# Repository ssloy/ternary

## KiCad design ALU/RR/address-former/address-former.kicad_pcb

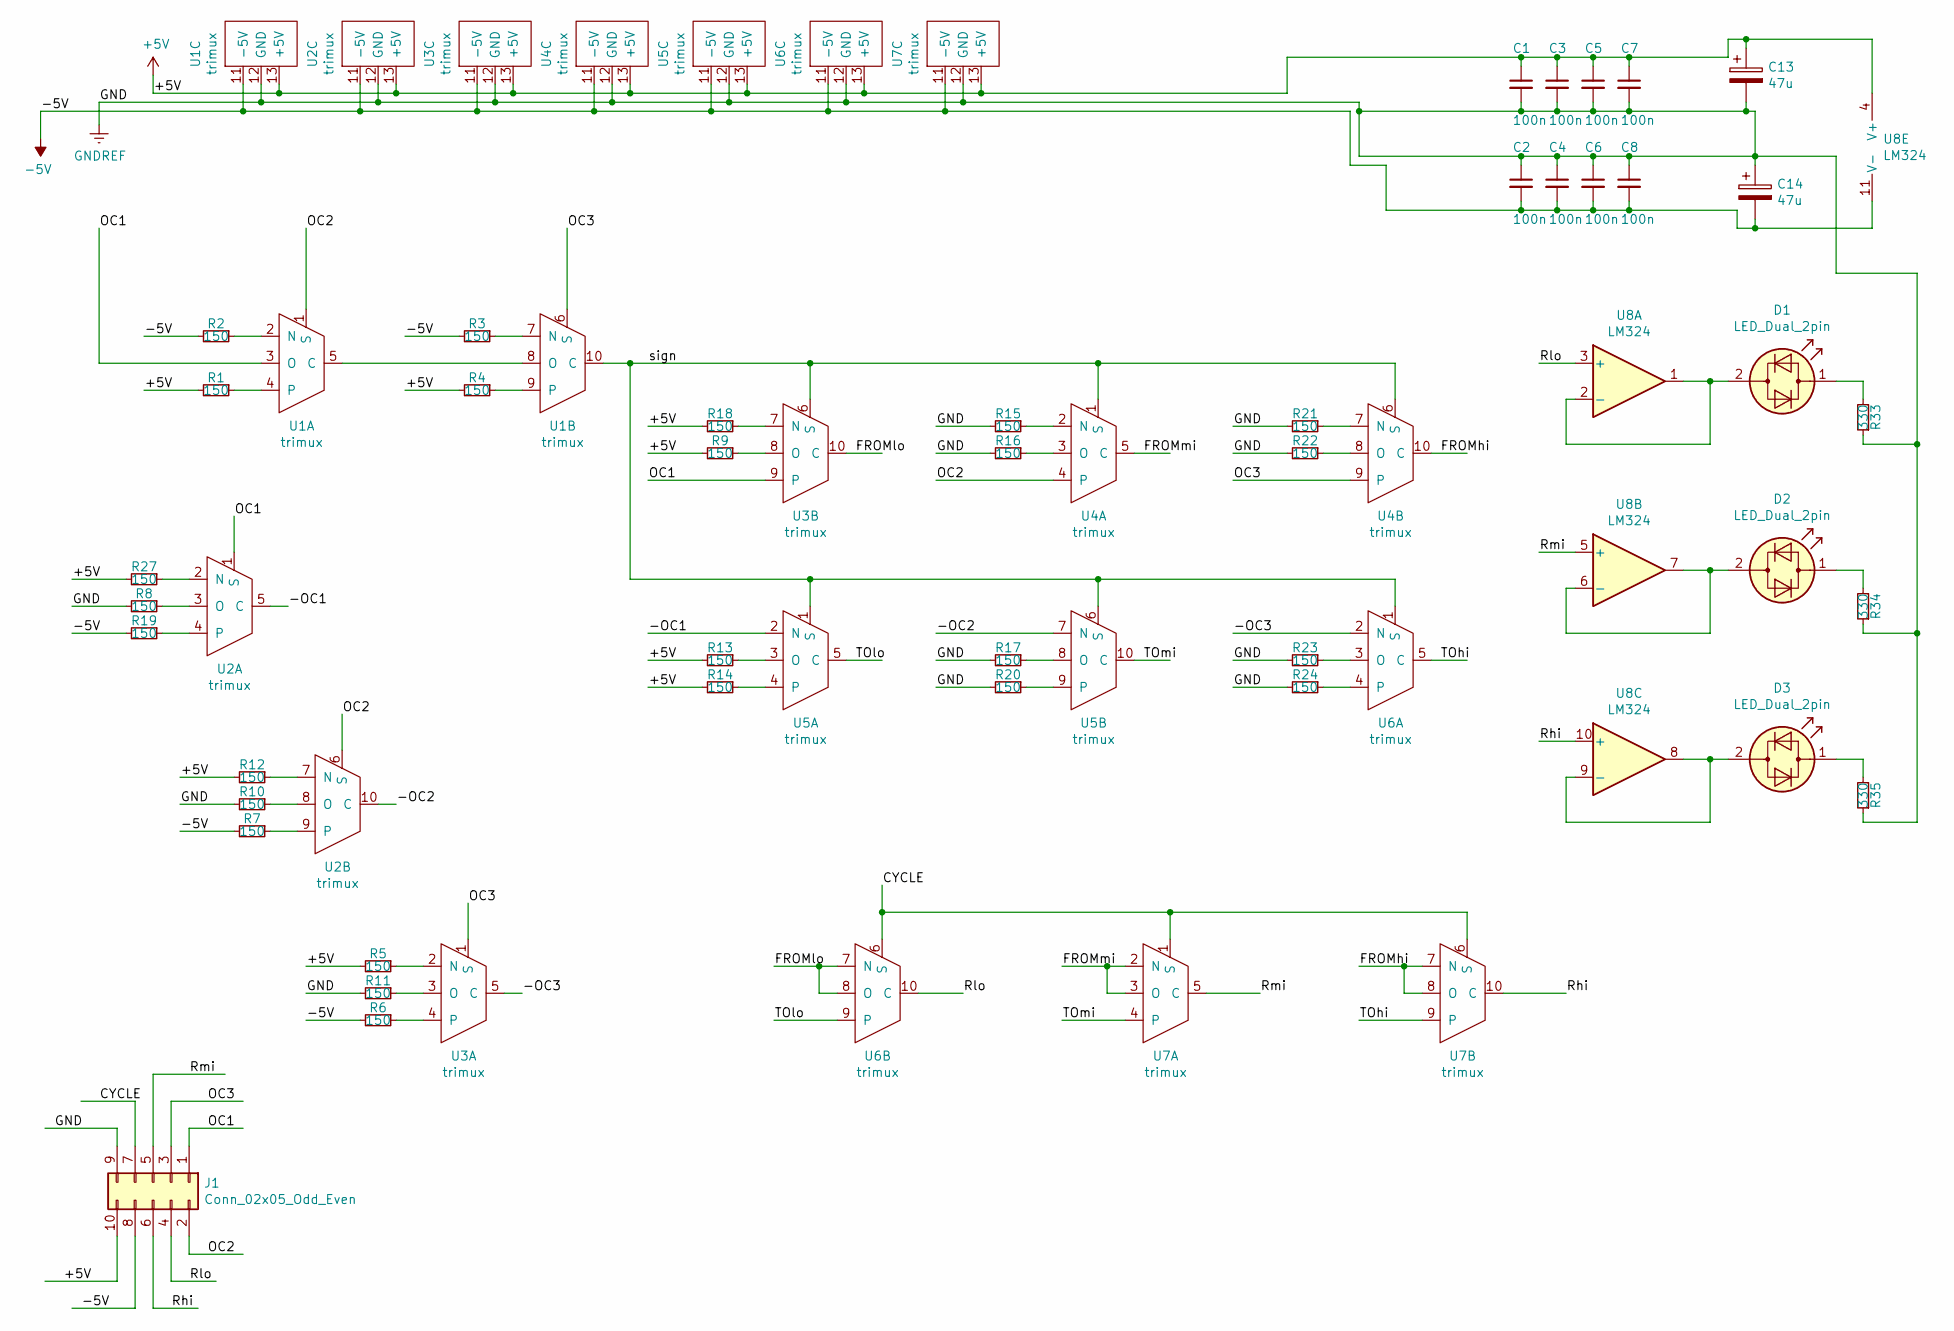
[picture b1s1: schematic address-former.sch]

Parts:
C1, C2, C3, C4, C5, C6, C7, C8: 100n; C_1206_3216Metric
C13, C14: 47u; CP_Radial_D5.0mm_P2.50mm
D1, D2, D3: LED_Dual_2pin; LED_D5.0mm
J1: Conn_02x05_Odd_Even; IDC-Header_2x05_P2.54mm_Vertical
R1, R2, R3, R4, R5, R6, R7, R8, R9, R10, R11, R12, R13, R14, R15, R16, R17, R18, R19, R20, R21, R22, R23, R24, R27: 150; R_1206_3216Metric
R33, R34, R35: 330; R_1206_3216Metric
U1, U2, U3, U4, U5, U6, U7: trimux; trimux1x15_2.54
U8: LM324; SOIC-14_3.9x8.7mm_P1.27mm

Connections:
/+5V: C1.1, C3.1, C5.1, C7.1, C13.1, J1.10, R1.2, R4.2, R5.2, R9.2, R12.2, R13.2, R14.2, R18.2, R27.2, U1.13 (+5V), U2.13 (+5V), U3.13 (+5V), U4.13 (+5V), U5.13 (+5V), U6.13 (+5V), U7.13 (+5V), U8.4 (V+)
/-5V: C2.2, C4.2, C6.2, C8.2, C14.2, J1.8, R2.2, R3.2, R6.2, R7.2, R19.2, U1.11 (-5V), U2.11 (-5V), U3.11 (-5V), U4.11 (-5V), U5.11 (-5V), U6.11 (-5V), U7.11 (-5V), U8.11 (V-)
/-OC1: U2.5 (C), U5.2 (N)
/-OC2: U2.10 (C), U5.7 (N)
/-OC3: U3.5 (C), U6.2 (N)
/CYCLE: J1.7, U6.6 (S), U7.1 (S), U7.6 (S)
/FROMhi: U4.10 (C), U7.7 (N), U7.8 (O)
/FROMlo: U3.10 (C), U6.7 (N), U6.8 (O)
/FROMmi: U4.5 (C), U7.2 (N), U7.3 (O)
/GND: C1.2, C2.1, C3.2, C4.1, C5.2, C6.1, C7.2, C8.1, C13.2, C14.1, J1.9, R8.2, R10.2, R11.2, R15.2, R16.2, R17.2, R20.2, R21.2, R22.2, R23.2, R24.2, R33.1, R34.1, R35.1, U1.12 (GND), U2.12 (GND), U3.12 (GND), U4.12 (GND), U5.12 (GND), U6.12 (GND), U7.12 (GND)
/OC1: J1.1, U1.3 (O), U2.1 (S), U3.9
/OC2: J1.2, U1.1 (S), U2.6 (S), U4.4
/OC3: J1.3, U1.6 (S), U3.1 (S), U4.9
/Rhi: J1.6, U7.10 (C), U8.10 (+)
/Rlo: J1.4, U6.10 (C), U8.3 (+)
/Rmi: J1.5, U7.5 (C), U8.5 (+)
/TOhi: U6.5 (C), U7.9
/TOlo: U5.5 (C), U6.9
/TOmi: U5.10 (C), U7.4
/sign: U1.10 (C), U3.6 (S), U4.1 (S), U4.6 (S), U5.1 (S), U5.6 (S), U6.1 (S)
unnamed: D1.1 (KA), R33.2
unnamed: D1.2 (AK), U8.1, U8.2 (-)
unnamed: D2.1 (KA), R34.2
unnamed: D2.2 (AK), U8.6 (-), U8.7
unnamed: D3.1 (KA), R35.2
unnamed: D3.2 (AK), U8.8, U8.9 (-)
unnamed: R1.1, U1.4
unnamed: R2.1, U1.2 (N)
unnamed: R3.1, U1.7 (N)
unnamed: R4.1, U1.9
unnamed: R5.1, U3.2 (N)
unnamed: R6.1, U3.4
unnamed: R7.1, U2.9
unnamed: R8.1, U2.3 (O)
unnamed: R9.1, U3.8 (O)
unnamed: R10.1, U2.8 (O)
unnamed: R11.1, U3.3 (O)
unnamed: R12.1, U2.7 (N)
unnamed: R13.1, U5.3 (O)
unnamed: R14.1, U5.4
unnamed: R15.1, U4.2 (N)
unnamed: R16.1, U4.3 (O)
unnamed: R17.1, U5.8 (O)
unnamed: R18.1, U3.7 (N)
unnamed: R19.1, U2.4
unnamed: R20.1, U5.9
unnamed: R21.1, U4.7 (N)
unnamed: R22.1, U4.8 (O)
unnamed: R23.1, U6.3 (O)
unnamed: R24.1, U6.4
unnamed: R27.1, U2.2 (N)
unnamed: U1.5 (C), U1.8 (O)

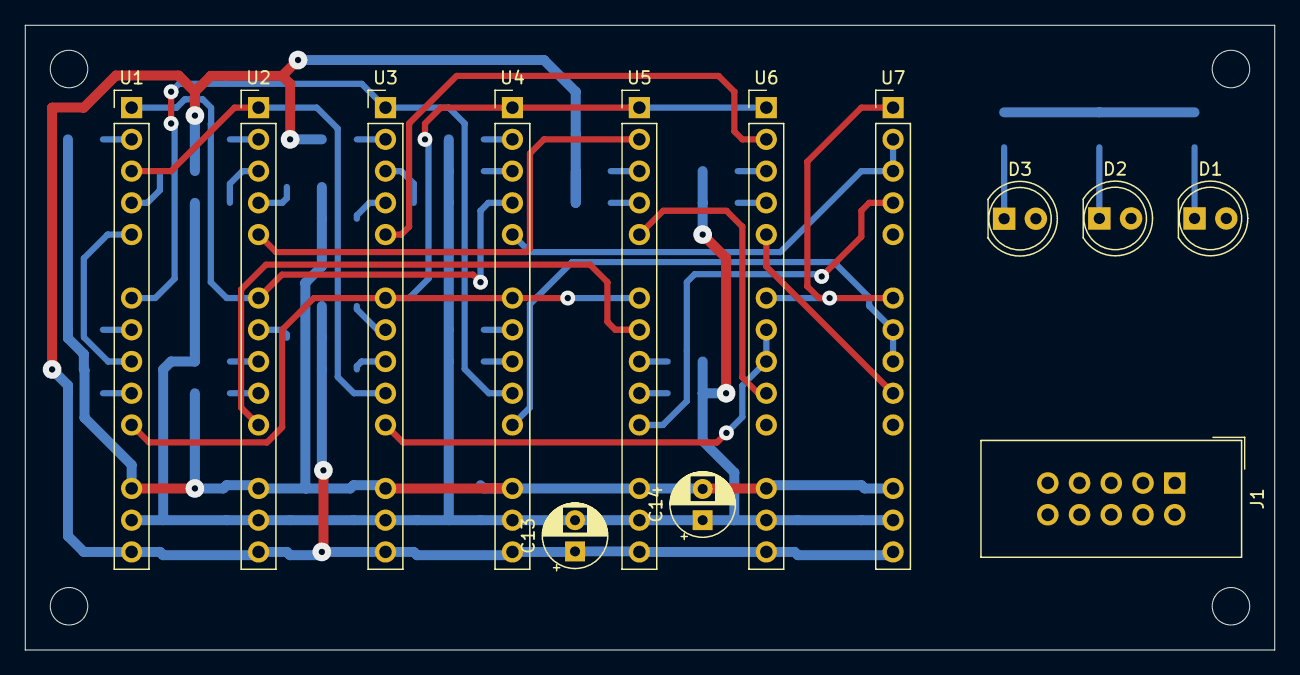
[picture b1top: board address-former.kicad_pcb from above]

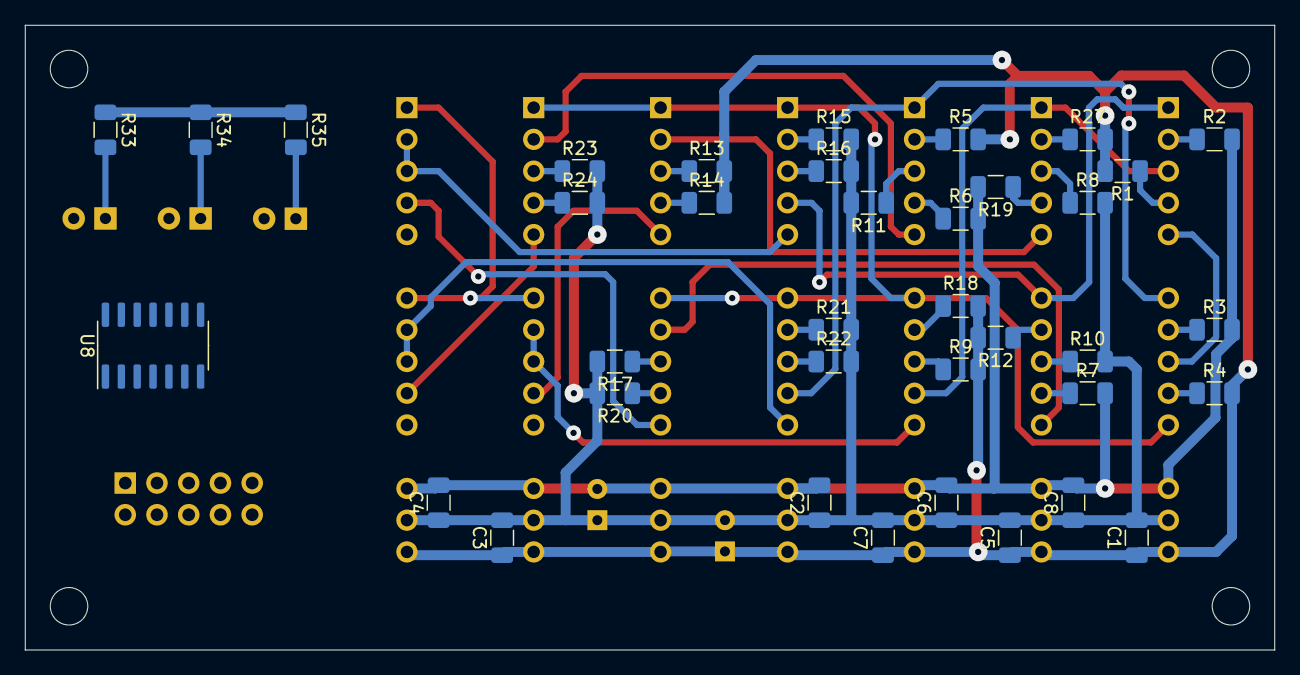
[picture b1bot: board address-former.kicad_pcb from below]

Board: 2 copper layers, 100.0 x 50.0 mm, 50 parts (37 on the bottom side), 52 nets.

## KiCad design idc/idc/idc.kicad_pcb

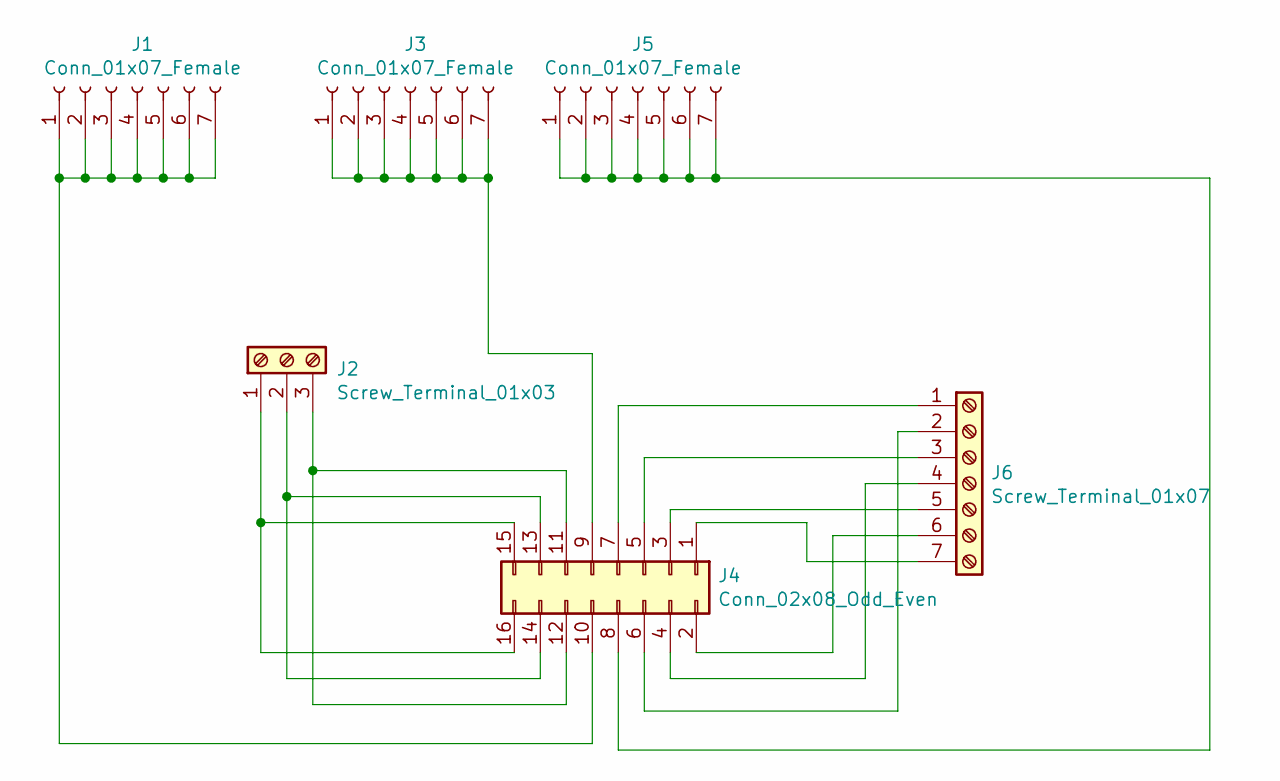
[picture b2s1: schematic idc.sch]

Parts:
J1, J3, J5: Conn_01x07_Female; PinHeader_1x07_P2.54mm_Vertical
J2: Screw_Terminal_01x03; TerminalBlock_TE_282834-3_1x03_P2.54mm_Horizontal
J4: Conn_02x08_Odd_Even; IDC-Header_2x08_P2.54mm_Vertical
J6: Screw_Terminal_01x07; TerminalBlock_Phoenix_MPT-0,5-7-2.54_1x07_P2.54mm_Horizontal

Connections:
unnamed: J1.1, J1.2, J1.3, J1.4, J1.5, J1.6, J1.7, J4.10
unnamed: J2.1, J4.15, J4.16
unnamed: J2.2, J4.13, J4.14
unnamed: J2.3, J4.11, J4.12
unnamed: J3.1, J3.2, J3.3, J3.4, J3.5, J3.6, J3.7, J4.9
unnamed: J4.1, J6.7
unnamed: J4.2, J6.6
unnamed: J4.3, J6.5
unnamed: J4.4, J6.4
unnamed: J4.5, J6.3
unnamed: J4.6, J6.2
unnamed: J4.7, J6.1
unnamed: J4.8, J5.1, J5.2, J5.3, J5.4, J5.5, J5.6, J5.7

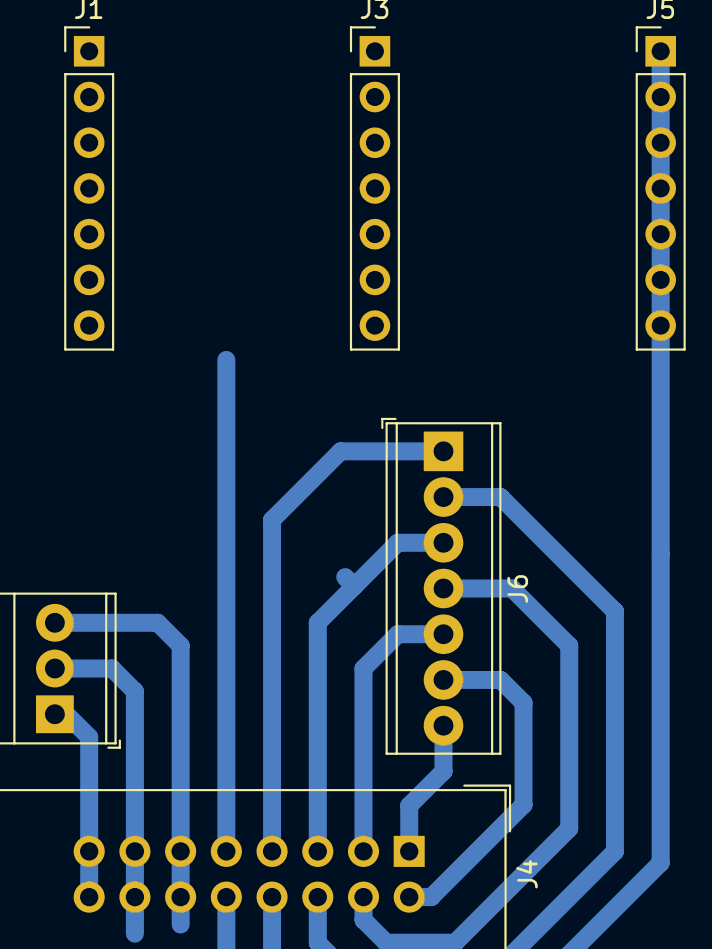
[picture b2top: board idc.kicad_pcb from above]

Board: 2 copper layers, 6 parts (0 on the bottom side), 13 nets.

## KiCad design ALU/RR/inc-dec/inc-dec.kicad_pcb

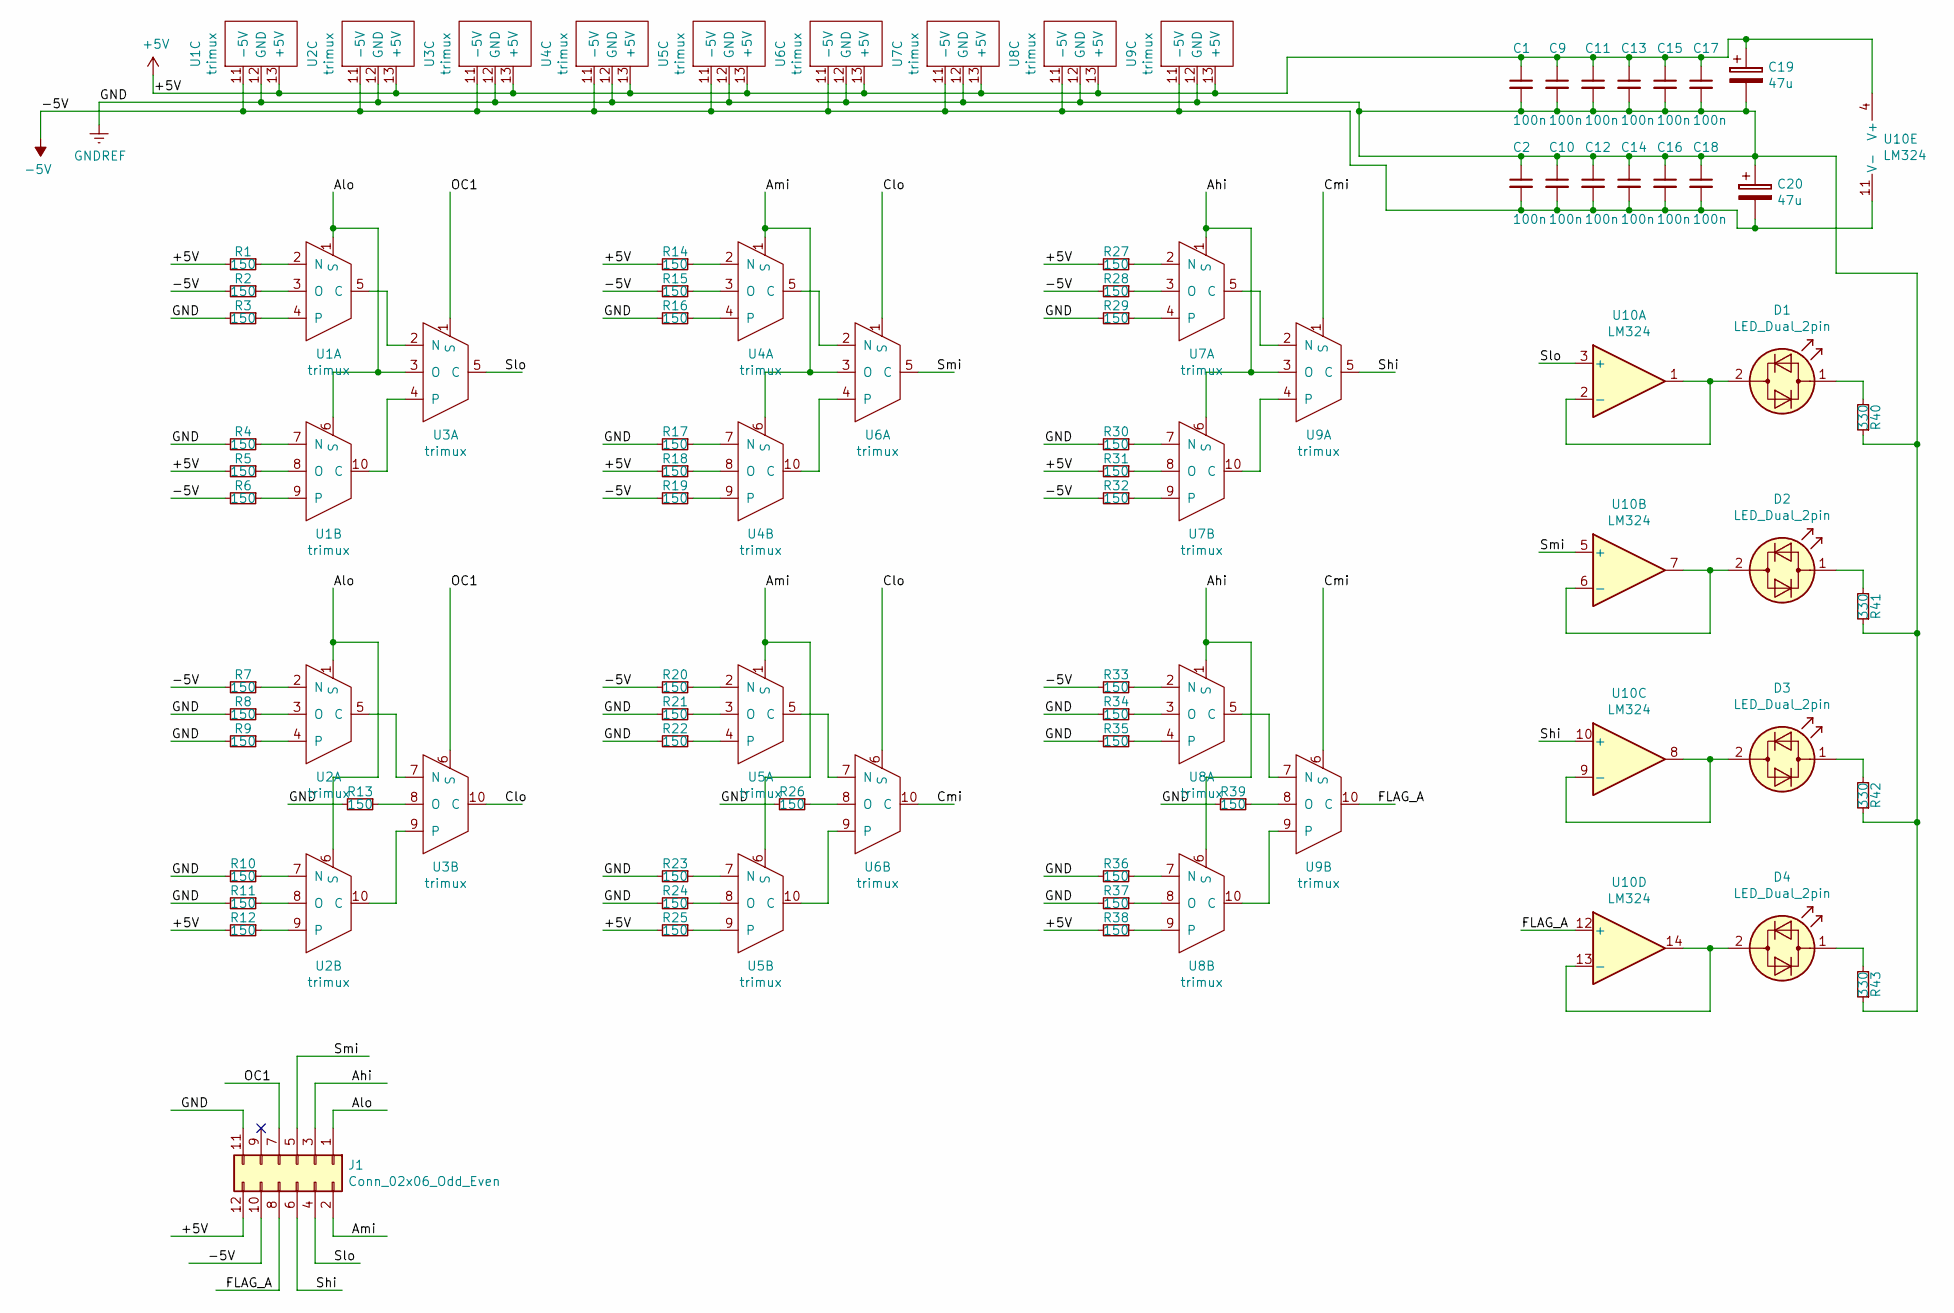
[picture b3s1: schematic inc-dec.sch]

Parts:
C1, C2, C9, C10, C11, C12, C13, C14, C15, C16, C17, C18: 100n; C_1206_3216Metric
C19, C20: 47u; CP_Radial_D5.0mm_P2.50mm
D1, D2, D3, D4: LED_Dual_2pin; LED_D5.0mm
J1: Conn_02x06_Odd_Even; IDC-Header_2x06_P2.54mm_Vertical
R1, R2, R3, R4, R5, R6, R7, R8, R9, R10, R11, R12, R13, R14, R15, R16, R17, R18, R19, R20, R21, R22, R23, R24, R25, R26, R27, R28, R29, R30, R31, R32, R33, R34, R35, R36, R37, R38, R39: 150; R_1206_3216Metric
R40, R41, R42, R43: 330; R_1206_3216Metric
U1, U2, U3, U4, U5, U6, U7, U8, U9: trimux; trimux1x15_2.54
U10: LM324; SOIC-14_3.9x8.7mm_P1.27mm

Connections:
/+5V: C1.1, C9.1, C11.1, C13.1, C15.1, C17.1, C19.1, J1.12, R1.2, R5.2, R12.2, R14.2, R18.2, R25.2, R27.2, R31.2, R38.2, U1.13 (+5V), U2.13 (+5V), U3.13 (+5V), U4.13 (+5V), U5.13 (+5V), U6.13 (+5V), U7.13 (+5V), U8.13 (+5V), U9.13 (+5V), U10.4 (V+)
/-5V: C2.2, C10.2, C12.2, C14.2, C16.2, C18.2, C20.2, J1.10, R2.2, R6.2, R7.2, R15.2, R19.2, R20.2, R28.2, R32.2, R33.2, U1.11 (-5V), U2.11 (-5V), U3.11 (-5V), U4.11 (-5V), U5.11 (-5V), U6.11 (-5V), U7.11 (-5V), U8.11 (-5V), U9.11 (-5V), U10.11 (V-)
/Ahi: J1.3, U7.1 (S), U7.6 (S), U8.1 (S), U8.6 (S), U9.3 (O)
/Alo: J1.1, U1.1 (S), U1.6 (S), U2.1 (S), U2.6 (S), U3.3 (O)
/Ami: J1.2, U4.1 (S), U4.6 (S), U5.1 (S), U5.6 (S), U6.3 (O)
/Clo: U3.10 (C), U6.1 (S), U6.6 (S)
/Cmi: U6.10 (C), U9.1 (S), U9.6 (S)
/FLAG_A: J1.8, U9.10 (C), U10.12 (+)
/GND: C1.2, C2.1, C9.2, C10.1, C11.2, C12.1, C13.2, C14.1, C15.2, C16.1, C17.2, C18.1, C19.2, C20.1, J1.11, R3.2, R4.2, R8.2, R9.2, R10.2, R11.2, R13.2, R16.2, R17.2, R21.2, R22.2, R23.2, R24.2, R26.2, R29.2, R30.2, R34.2, R35.2, R36.2, R37.2, R39.2, R40.1, R41.1, R42.1, R43.1, U1.12 (GND), U2.12 (GND), U3.12 (GND), U4.12 (GND), U5.12 (GND), U6.12 (GND), U7.12 (GND), U8.12 (GND), U9.12 (GND)
/OC1: J1.7, U3.1 (S), U3.6 (S)
/Shi: J1.6, U9.5 (C), U10.10 (+)
/Slo: J1.4, U3.5 (C), U10.3 (+)
/Smi: J1.5, U6.5 (C), U10.5 (+)
unnamed: D1.1 (KA), R40.2
unnamed: D1.2 (AK), U10.1, U10.2 (-)
unnamed: D2.1 (KA), R41.2
unnamed: D2.2 (AK), U10.6 (-), U10.7
unnamed: D3.1 (KA), R42.2
unnamed: D3.2 (AK), U10.8, U10.9 (-)
unnamed: D4.1 (KA), R43.2
unnamed: D4.2 (AK), U10.13 (-), U10.14
unnamed: R1.1, U1.2 (N)
unnamed: R2.1, U1.3 (O)
unnamed: R3.1, U1.4
unnamed: R4.1, U1.7 (N)
unnamed: R5.1, U1.8 (O)
unnamed: R6.1, U1.9
unnamed: R7.1, U2.2 (N)
unnamed: R8.1, U2.3 (O)
unnamed: R9.1, U2.4
unnamed: R10.1, U2.7 (N)
unnamed: R11.1, U2.8 (O)
unnamed: R12.1, U2.9
unnamed: R13.1, U3.8 (O)
unnamed: R14.1, U4.2 (N)
unnamed: R15.1, U4.3 (O)
unnamed: R16.1, U4.4
unnamed: R17.1, U4.7 (N)
unnamed: R18.1, U4.8 (O)
unnamed: R19.1, U4.9
unnamed: R20.1, U5.2 (N)
unnamed: R21.1, U5.3 (O)
unnamed: R22.1, U5.4
unnamed: R23.1, U5.7 (N)
unnamed: R24.1, U5.8 (O)
unnamed: R25.1, U5.9
unnamed: R26.1, U6.8 (O)
unnamed: R27.1, U7.2 (N)
unnamed: R28.1, U7.3 (O)
unnamed: R29.1, U7.4
unnamed: R30.1, U7.7 (N)
unnamed: R31.1, U7.8 (O)
unnamed: R32.1, U7.9
unnamed: R33.1, U8.2 (N)
unnamed: R34.1, U8.3 (O)
unnamed: R35.1, U8.4
unnamed: R36.1, U8.7 (N)
unnamed: R37.1, U8.8 (O)
unnamed: R38.1, U8.9
unnamed: R39.1, U9.8 (O)
unnamed: U1.5 (C), U3.2 (N)
unnamed: U1.10 (C), U3.4
unnamed: U2.5 (C), U3.7 (N)
unnamed: U2.10 (C), U3.9
unnamed: U4.5 (C), U6.2 (N)
unnamed: U4.10 (C), U6.4
unnamed: U5.5 (C), U6.7 (N)
unnamed: U5.10 (C), U6.9
unnamed: U7.5 (C), U9.2 (N)
unnamed: U7.10 (C), U9.4
unnamed: U8.5 (C), U9.7 (N)
unnamed: U8.10 (C), U9.9

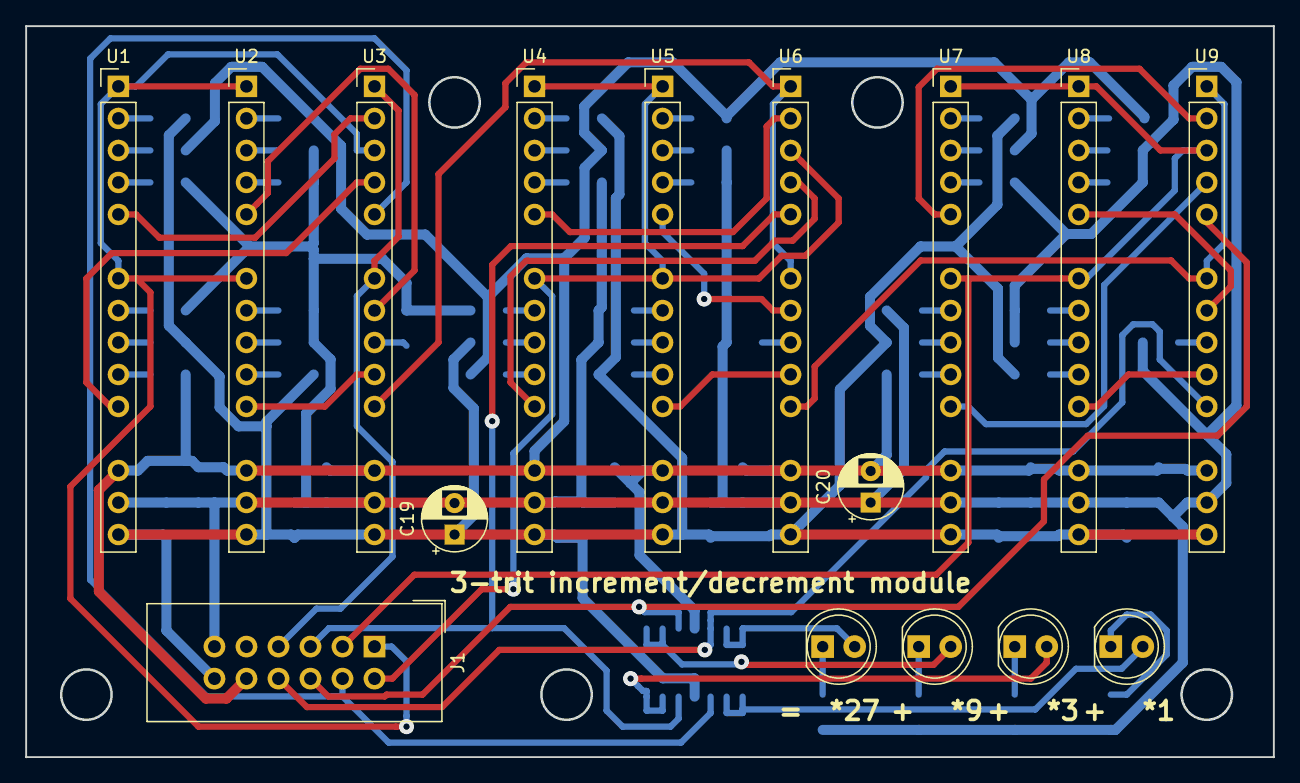
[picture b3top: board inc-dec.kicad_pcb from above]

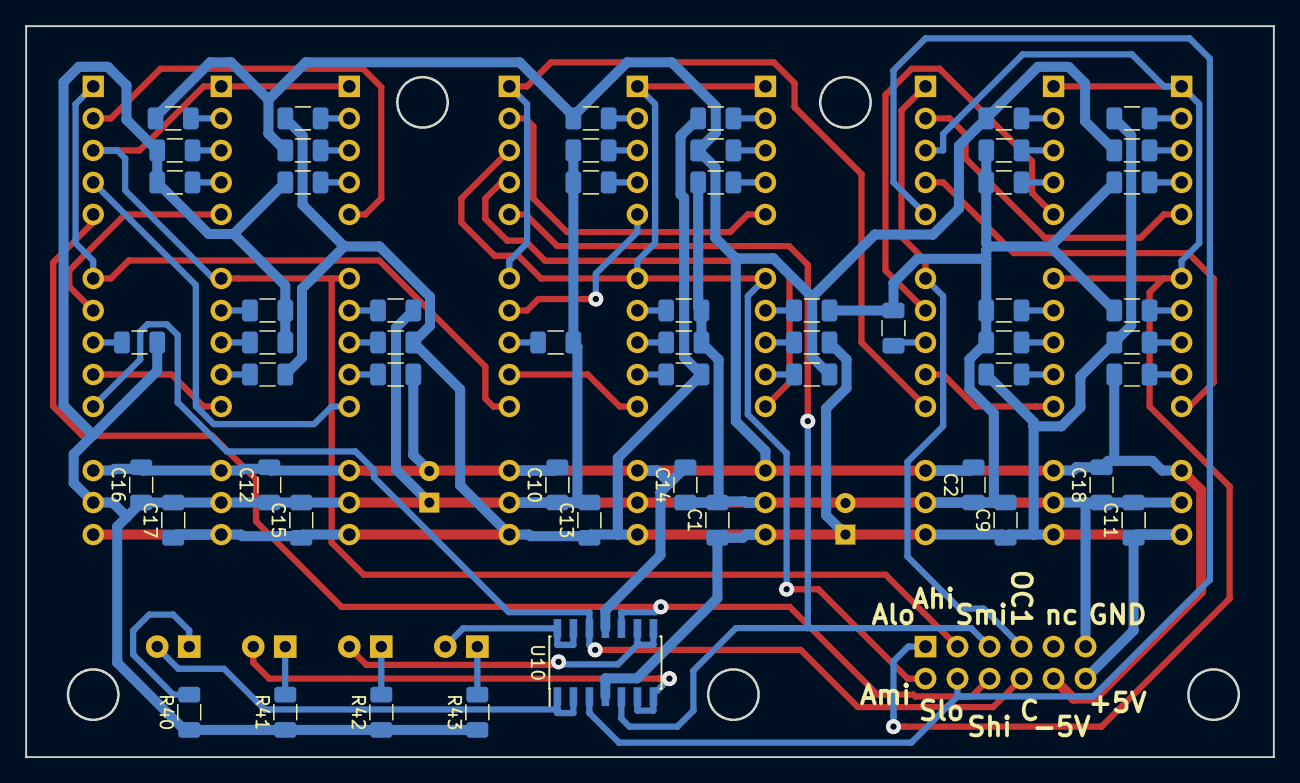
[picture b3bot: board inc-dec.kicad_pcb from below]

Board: 2 copper layers, 99.0 x 58.0 mm, 72 parts (56 on the bottom side), 72 nets.

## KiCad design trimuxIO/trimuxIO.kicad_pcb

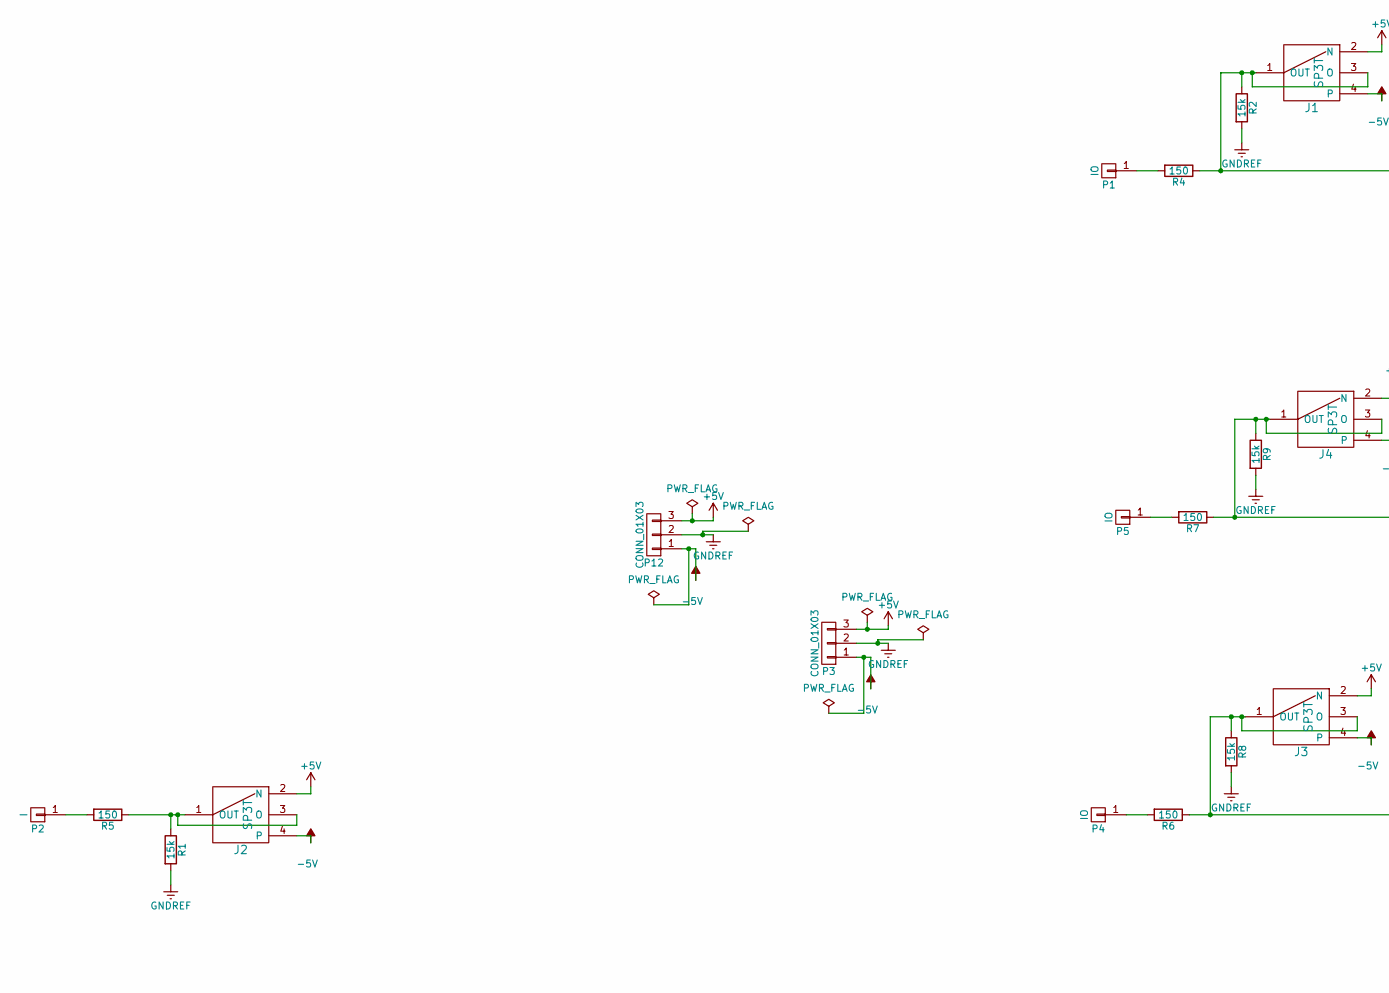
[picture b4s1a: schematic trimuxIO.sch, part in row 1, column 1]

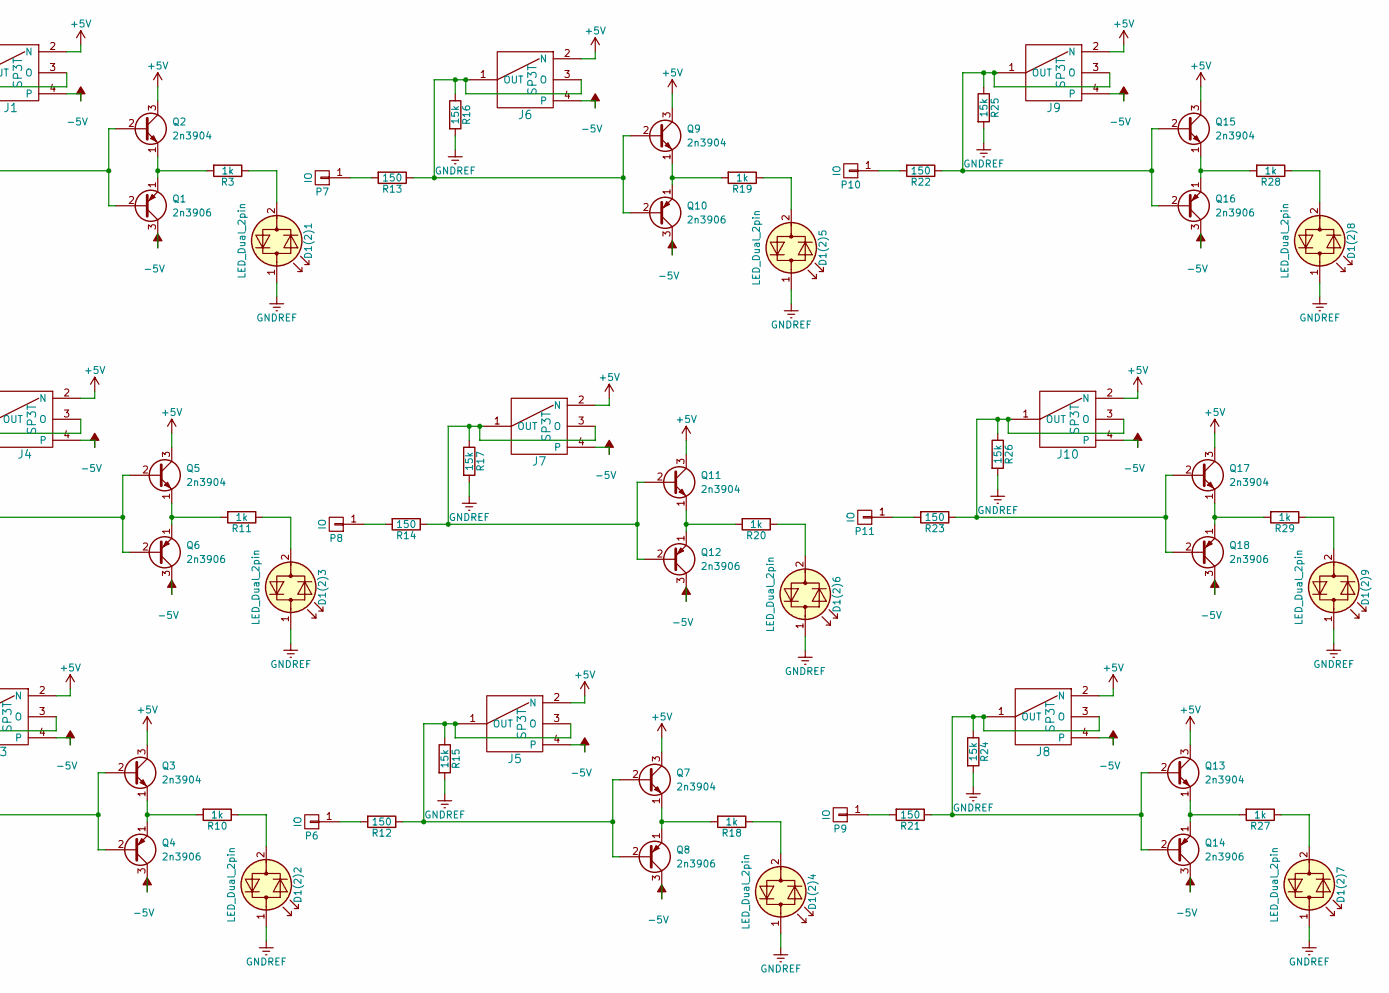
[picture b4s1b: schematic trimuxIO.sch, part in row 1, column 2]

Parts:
D1(2)1, D1(2)2, D1(2)3, D1(2)4, D1(2)5, D1(2)6, D1(2)7, D1(2)8, D1(2)9: LED_Dual_2pin; LED_D5.0mm
J1, J2, J3, J4, J5, J6, J7, J8, J9, J10: SP3T; Pin_Header_Straight_1x04_Pitch3.10mm
P1, P4, P5, P6, P7, P8, P9, P10, P11: IO; Pin_Header_Straight_1x01_Pitch2.54mm
P2: I; Pin_Header_Straight_1x01_Pitch2.54mm
P3, P12: CONN_01X03; Pin_Header_Straight_1x03_Pitch2.54mm
Q1, Q4, Q6, Q8, Q10, Q12, Q14, Q16, Q18: 2n3906; TO-92_Inline_Wide
Q2, Q3, Q5, Q7, Q9, Q11, Q13, Q15, Q17: 2n3904; TO-92_Inline_Wide
R1, R2, R8, R9, R15, R16, R17, R24, R25, R26: 15k; R_Axial_DIN0411_L9.9mm_D3.6mm_P15.24mm_Horizontal
R3, R10, R11, R18, R19, R20, R27, R28, R29: 1k; R_Axial_DIN0411_L9.9mm_D3.6mm_P15.24mm_Horizontal
R4, R5, R6, R7, R12, R13, R14, R21, R22, R23: 150; R_Axial_DIN0411_L9.9mm_D3.6mm_P15.24mm_Horizontal

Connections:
+5V: J1.2 (N), J2.2 (N), J3.2 (N), J4.2 (N), J5.2 (N), J6.2 (N), J7.2 (N), J8.2 (N), J9.2 (N), J10.2 (N), P3.3, P12.3, Q2.3 (C), Q3.3 (C), Q5.3 (C), Q7.3 (C), Q9.3 (C), Q11.3 (C), Q13.3 (C), Q15.3 (C), Q17.3 (C); also elsewhere on the board
-5V: J1.4, J2.4, J3.4, J4.4, J5.4, J6.4, J7.4, J8.4, J9.4, J10.4, P3.1, P12.1, Q1.3 (C), Q4.3 (C), Q6.3 (C), Q8.3 (C), Q10.3 (C), Q12.3 (C), Q14.3 (C), Q16.3 (C), Q18.3 (C); also elsewhere on the board
GNDREF: D1(2)1.1 (KA), D1(2)2.1 (KA), D1(2)3.1 (KA), D1(2)4.1 (KA), D1(2)5.1 (KA), D1(2)6.1 (KA), D1(2)7.1 (KA), D1(2)8.1 (KA), D1(2)9.1 (KA), P3.2, P12.2, R1.2, R2.2, R8.2, R9.2, R15.2, R16.2, R17.2, R24.2, R25.2, R26.2; also elsewhere on the board
unnamed: D1(2)1.2 (AK), R3.1
unnamed: D1(2)2.2 (AK), R10.1
unnamed: D1(2)3.2 (AK), R11.1
unnamed: D1(2)4.2 (AK), R18.1
unnamed: D1(2)5.2 (AK), R19.1
unnamed: D1(2)6.2 (AK), R20.1
unnamed: D1(2)7.2 (AK), R27.1
unnamed: D1(2)8.2 (AK), R28.1
unnamed: D1(2)9.2 (AK), R29.1
unnamed: J1.1 (OUT), J1.3 (O), Q1.2 (B), Q2.2 (B), R2.1, R4.1
unnamed: J2.1 (OUT), J2.3 (O), R1.1, R5.1
unnamed: J3.1 (OUT), J3.3 (O), Q3.2 (B), Q4.2 (B), R6.1, R8.1
unnamed: J4.1 (OUT), J4.3 (O), Q5.2 (B), Q6.2 (B), R7.1, R9.1
unnamed: J5.1 (OUT), J5.3 (O), Q7.2 (B), Q8.2 (B), R12.1, R15.1
unnamed: J6.1 (OUT), J6.3 (O), Q9.2 (B), Q10.2 (B), R13.1, R16.1
unnamed: J7.1 (OUT), J7.3 (O), Q11.2 (B), Q12.2 (B), R14.1, R17.1
unnamed: J8.1 (OUT), J8.3 (O), Q13.2 (B), Q14.2 (B), R21.1, R24.1
unnamed: J9.1 (OUT), J9.3 (O), Q15.2 (B), Q16.2 (B), R22.1, R25.1
unnamed: J10.1 (OUT), J10.3 (O), Q17.2 (B), Q18.2 (B), R23.1, R26.1
unnamed: P1.1, R4.2
unnamed: P2.1, R5.2
unnamed: P4.1, R6.2
unnamed: P5.1, R7.2
unnamed: P6.1, R12.2
unnamed: P7.1, R13.2
unnamed: P8.1, R14.2
unnamed: P9.1, R21.2
unnamed: P10.1, R22.2
unnamed: P11.1, R23.2
unnamed: Q1.1 (E), Q2.1 (E), R3.2
unnamed: Q3.1 (E), Q4.1 (E), R10.2
unnamed: Q5.1 (E), Q6.1 (E), R11.2
unnamed: Q7.1 (E), Q8.1 (E), R18.2
unnamed: Q9.1 (E), Q10.1 (E), R19.2
unnamed: Q11.1 (E), Q12.1 (E), R20.2
unnamed: Q13.1 (E), Q14.1 (E), R27.2
unnamed: Q15.1 (E), Q16.1 (E), R28.2
unnamed: Q17.1 (E), Q18.1 (E), R29.2

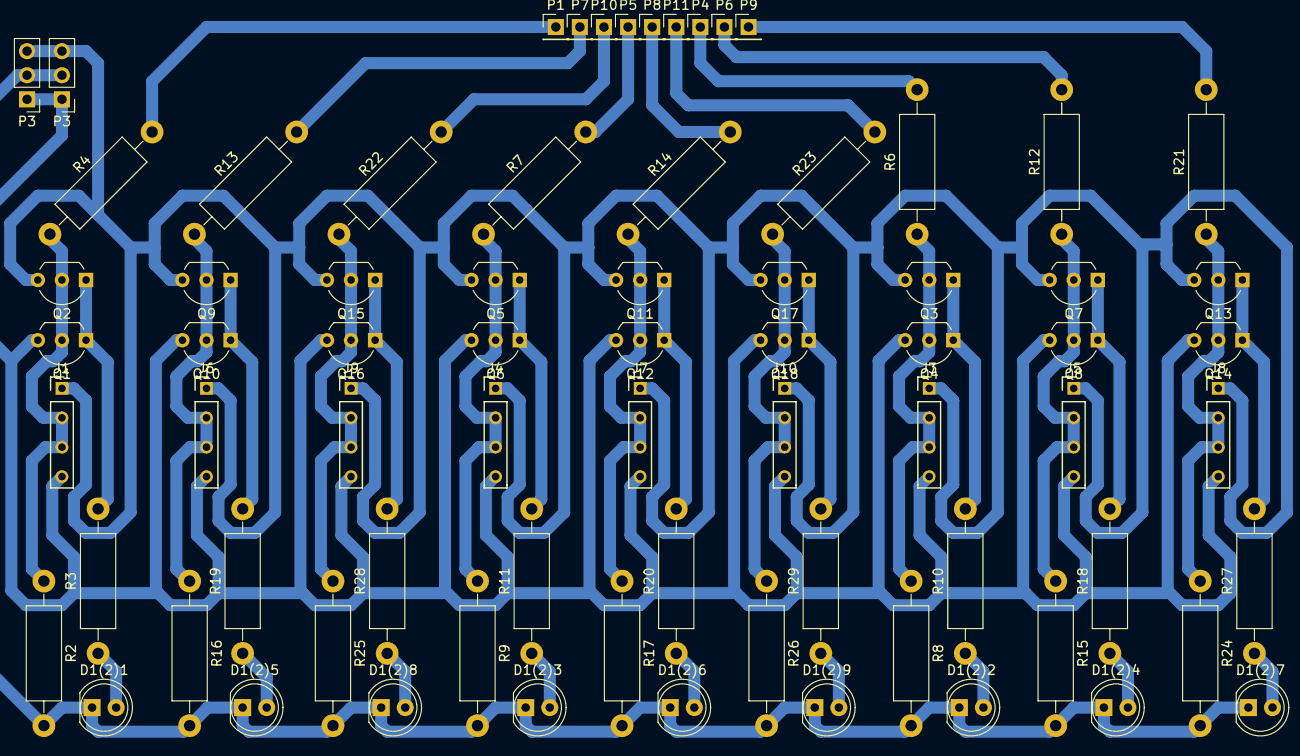
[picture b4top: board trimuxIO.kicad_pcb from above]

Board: 2 copper layers, 74 parts (0 on the bottom side), 39 nets.

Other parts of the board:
P3#2: CONN_01X03; Pin_Header_Straight_1x03_Pitch2.54mm

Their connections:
+5V: P3#2.3; also elsewhere on the board
-5V: P3#2.1; also elsewhere on the board
GNDREF: P3#2.2; also elsewhere on the board

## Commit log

2020-05-13 initial import
2020-05-14 RR address former stub
